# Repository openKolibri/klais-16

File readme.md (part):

![SIXTEEN]
![SEGMENT]
![DISPLAY]

# Sixteen Segment Display
The look of classic signage, be it neon tubes, wrought iron, or the use of distinctive typography and negative space, has a particular appeal. Unfortunately, the art form is dwindling due to the flexibility and flash that comes with newer LED arrays. Their distinctive styles have been giving way for the monotony of RGB LED panels.

![cycleGif]

The *Klais Display* series, in which this panel is the first item, was inspired by the early electronic displays still seen in relics bygone from an era of cigarette machines, electronics test equipment, and pinball machines. Its been modernized, enlarged, and made easily integrable into your own projects, while retaining its beauty and elegance.

![isoArray]

What follows below is highly detailed technical documentation. The [user guide][userGuide] is also available and focuses on integrating the display(s) into a project.

## Table of Contents
  * [Design](#design)
    * [Hardware](#hardware)
      * [LEDs](#leds)
      * [LED Driver](#led-driver)
      * [Microcontroller](#microcontroller)
      * [Power supply](#power-supply)
      * [Connections](#connections)
        * [Programming](#programming)
        * [Dataflow](#dataflow)
        * [Config Pads](#config-pads)
        * [Key Connector](#key-connector)
      * [Mounting](#mounting)
    * [Firmware](#firmware)
      * [Modes](#modes)
      * [UART](#uart)
        * [RX](#rx)
        * [TX](#tx)
      * [Brightness](#brightness)
      * [Timeout Refresh](#timeout-refresh)
      * [Display Driver](#display-driver)
        * [Protocol](#protocol)
        * [LED Number](#led-number)
        * [Segment Order](#segment-order)
      * [Configuration](#configuration)
        * [Baud Selection](#baud-selection)
      * [Compiling](#compiling)
      * [Flashing](#flashing)
  * [Absolute Maximum Ratings](#absolute-maximum-ratings)
  * [Guaranteed Ratings](#guaranteed-ratings)
  * [Manufacturing](#manufacturing)
    * [BOM](#bom)
    * [PCB-Assembly](#pcb-assembly)
    * [Physical Assembly](#physical-assembly)
    * [Production Scaling](#production-scaling)
      * [PCB Stack](#pcb-stack)
      * [Die Cut](#die-cut)
      * [Injection Moulding](#injection-moulding)
      * [Custom ASIC](#custom-asic)
    * [Programmer](#programmer)
      * [Minimal](#minimal)
      * [Production](#production)
    * [Artwork](#artwork)
    * [Labels](#labels)
    * [Inventory and QC](#inventory-and-qc)
    * [Part Numbers](#part-numbers)
  * [Safety](#safety)
  * [Certifications](#certifications)
  * [Licence](#licence)
  * [Attribution](#attribution)
    * [Fonts](#fonts)
    * [Libraries](#libraries)
  * [Reccomended Reading](#reccomended-reading)
  * [ToDo](#todo)

## Design
The display is a recreation of sixteen segment alphanumeric displays in a format that is physically larger and thinner than anything available on the viewing front. The modular segments can be combined to make a display of any length. It is designed to be easy to use and accessible. The physical design is based on stacking layers to provide clearance, a diffusion layer, and encapsulation for the electronics. The minimalist design and 3:2 aspect ratio were chosen to make integration very clean. There are no gaps between characters and when placed side-by-side, there is a flat near-seamless surface.

| NOON               | MDNT               | BASE               |
| ------------------ | ------------------ | ------------------ |
| ![SEG-16-RED-NOON] | ![SEG-16-RED-MDNT] | ![SEG-16-RED-BASE] |

### Hardware
The panels are designed for efficient high yield manufacturing in both small and large quantities, with three possible stages, based on tooling investment. The physical size of each panel is `100 mm` x `66.66 mm`, providing a 3:2 aspect ratio and are nominally `5.8 mm` thick. Each panel weighs `63.97 g` with 6 plastic rivets.

![schematic]

A [schematic.pdf] is also available.

#### LEDs
The assembly uses 128 0603 surface mount LEDs. They are spaced evenly through all the segments, as well as eight of them acting as points in the underline. The 0603 (`60 mil` x `30 mil`, or `1.5 mm` x `0.8 mm`) package is used for their wide accessibility, providing a breadth of alternatives in color, lens projection angle, and brightness for possible substitutions. The datasheets for the LEDs used for each model is provided in the table below.

| Model             | MPN        | Detail          | Current Draw         |
| ----------------- | ---------- | --------------- | -------------------- |
| `SEG-16-RED-XXXX` | [KT-0603R] | ![IMG-KT-0603R] | [RED][asciiCurrent]  |

#### Led Driver
Titan Micro Electronic's [TM1640] ([english][TM1640ENG]) is used to control the LEDs. The device provides individual control of 128 LEDs in a 16x8 multiplexing configuration, has 8 levels of brightness adjustment, and provides a constant current supply of `20 mA`. It is rated for only `5V` but testing shows that, although with a slightly lower multiplexing frequency, it works quite well at `3.3V`. Communication is over a clocked serial link with a custom protocol and register mappings control the outputs. The 16 grids are rows, while the eight segments are the columns.

![IMG-TM1640]

This chip is made specifically for the Chinese market and may be hard to source in the west. Based on datasheets, it is easily swappable with identical components from other manufacturers, as shown below, in case the availability changes.

| Manufacturer            | MPN      |
| ----------------------- | -------- |
| GN Semiconductors       | GN1640   |
| Cmsemicon               | CMS1640  |
| Wuxi I-CORE Electronics | AiP1640  |

#### Microcontroller
STMicroelectronics's [STM8S003] is a very low-cost microcontroller for cost sensitive applications, but provides a reasonable host of features. It has a wide voltage range of `2.95V` to `5.5V`, internal 16Mhz clock, UART that can be clocked at up to 1Mbps, plenty of timers, and 28 I/O. As well as other features that are not being used like a 10b ADC, SPI/I2C hardware, and low power modes.

![IMG-STM8S003]

#### Power supply
The input power is rated at `5V`, and the current drawn is dependent on the number of lit LEDs and the color of the display. Each segment has `100 uF` + `10 uF` of bulk capacitance, as well as decoupling on all the chips so it should be robust against a unstable power supply. There is no reverse polarity or overvoltage protection as that is the responsibility of the integrator. The table below shows some current draws, with the full table of all the models and characters [available][asciiCurrent] along with measurement methodology.

| Display  | `RED` Full Brightness (mA) | `RED` Min Brightness (mA) |
| -------- | --------------------------:| -------------------------:|
| Off      |                        5.2 |                       5.2 |
| All      |                      319.0 |                      28.6 |
| `@`      |                      197.0 |                      19.1 |
| `.`      |                       17.1 |                       6.0 |
| `K`      |                      125.7 |                      13.8 |
| `[`      |                      106.0 |                      12.4 |

Maximum power draw is `1.6 W` at max brightness and all segments lit. Temperature rise above ambient after two hours is `15.9°C` (`61°F`).

#### Connections
The back of the module contains pads that are used for communication and configuration, providing many options to the end-user.

![config-back]

##### Programming
The four labeled pads near the top of the module are for programming. The STM8S uses a `SWIM` programming interface. The `4 mm` round pads are used to install the initial firmware and can be used for firmware updates or custom firmware if needed. The power pins are connected to the power rails, so they can also be used as power input or outputs.

![config-pgrm]

##### Dataflow
The five pads on each side are the connections that provide the data, as well as power rails, from one board to another. For basic functionality, lining up the boards and soldering the top three pads (`GND`, `TX/RX`, and `+5V`) is all that is needed, although soldering all five will provide more power rails and cause no issues.

![config-dataflow]

With the display facing you, the data comes in on the left on the `RX` pad, and flows out on the right via the `TX` pad. If the modules are soldered inverted, the connection is symmetric providing protection against swapping power supply rails.

If needed, the inverted configuration also provides the option of having two decimal points forming a colon. For this configuration to work, the solder jumper pads on the back will need to be reconfigured, cutting the top two and bridging the bottom, as shown in the diagram.

![config-dataflowInv]

The moves the `RX` and `TX` lines to the correct sides to be placed inline with normally oriented modules.

##### Config Pads
The back has seven configuration pads that provide different settings and are checked on boot. By default, they are all unbridged. The configuration pads are to be selected with solder jumpers.

![config-config]

##### Key Connector
The front contains two optional unpopulated spring connectors Molex [0472861001]. These provide functionality if the thickness of the panel or reconfigurability is the main concern. By removing any solder joints on the back, and transmitting the data and power through the keyed connector. The thickness is limited to `5.8 mm`. The small PCB keys also allow assembly and construction of quick and easily reconfigurable arrays. The connectors are not always used, so they are not installed by default since they add cost and are not expected to be used by most.

![config-keyed]

The solder jumper marked `RTN_EN` enables the return channel on the last board. If a chain of displays is used and needs to be chained to the next row, this will send the signal back though one of the spring connector pins and make it available on the first display making a for a cleaner run of signal between rows.

#### Mounting
The mounting holes are placed `3 mm` from all edges and are for `M3` screws in a very close fit with a `3.1 mm` drill and though plated for a bit more ruggedness. A `#4` screw can be used as a imperial alternative. They are not connected to any nets, have a `5.5 mm` annular ring for screw heads, and are masked so if screws are not used, the annular ring surface matches the rest of the panel.

![mountingDim]

The holes and hardware provide a number of options for assembly and mounting.

| Mounting Method              | Part Number                                      | Component         | Example               |
| ---------------------------- | ------------------------------------------------ | ----------------- | --------------------- |
| Push Rivet `3 mm` x `7.5 mm` | [R3075]                                          | ![plasticRivet]   | ![rivetInstalled]     |
| Spring pin `3 mm` x `6 mm`   | [97161A128]                                      | ![springPin]      | ![springPinInstalled] |
| `M3x8x0.5` and Nut           | [91292A112] [91828A211]                          | ![M3x8]           | ![M3x8Installed]      |
| `15 mm` Extrusion M3x10      | [Misumi HFS3], [OpenBeam], [Makerbeam XL]        | ![openbeamParts]  | ![openbeamInstalled]  |
| `10 mm` Extruison M3x8       | [MakerBeam], [MicroRAX]                          | ![makerbeamParts] | ![makerbeamInstalled] |
| `20 mm` Extrusion Slot       | [Misumi HFS5], [Metric 8020]                     | ![2020Extrusion]  | ![2020Installed]      |
| Soldered brass nut           | [90690A037]                                      |                   |                       |
| Zip Ties `3 mm`              |                                                  |                   |                       |
| #4 screw, machine or wood    |                                                  |                   |                       |
| Pop rivets, M3 or #4         |                                                  |                   |                       |

### Firmware
The firmware is written in C and is fully interrupt driven. It uses the [STM8 standard periphiral library][STM8SPL] (SPL) and provides multiple modes of controlling the display through commands. All code shown is simplified pseudocode.

#### Modes
By default the display boots in the `ASCII` character mode operating as a state-machine making changes based on each byte received. When enough bytes have been received for the command, the device shifts back into `ASCII` mode.

| Mode       | Control Byte | Bytes | Notes                       |
| ---------- | ------------ | -----:| --------------------------- |
| ASCII      | None         |     0 | Displays ASCII cahrachter   |
| Segment    | 0x11 `DC1`   |     3 | Control individual segments |
| LED        | 0x12 `DC2`   |    16 | Control individual LEDs     |
| Brightness | 0x13 `DC3`   |     1 | Set brightness              |

**Only ASCII mode is verified in firmware version 0.6 other modes are in beta**

#### UART
The UART hardware is used to receive and transmit data from a module to another. Communication is through an 8 bit NRZ with one start bit and one stop bit encoding with no parity and the default baud rate is `115200 bps`. The voltage levels are the module power voltage, nominally `5V`.

The UART is initialized on boot and the receive interrupt is enabled. When a new character has been read in the receive buffer, the interrupt fires.

##### RX
Based on the receive mode the new data is loaded into the receive buffer. A number of consecutive bytes read is dependent on the mode that is set. A mode byte received after mode has been reset will change the mode as well. The transmit interrupt is fired when a new byte is received and the buffer is full, depending on the current receive mode.

##### TX
The first byte is sent by the interrupt trigger. Depending on the transmit mode, the interrupts continue to fire, stepping down through the buffer until it is empty, outputting the data in the same order as it was received.

#### Brightness
There are nine brightness levels including blanking. They are accessed with sending the brightness mode selector followed by the brightness code.

| Level | Code (HEX) | Code (DEC) |
| -----:| ---------- | ----------:|
|   OFF | 0x81       |        129 |
|     1 | 0x88       |        136 |
|     2 | 0x89       |        137 |
|     4 | 0x8A       |        138 |
|    10 | 0x8B       |        139 |
|    11 | 0x8C       |        140 |
|    12 | 0x8D       |        141 |
|    13 | 0x8E       |        142 |
|    14 | 0x8F       |        143 |

#### Timeout Refresh
A display refresh timeout is implemented so the display only updates when there is a pause in the data. This prevents the display from flickering with intermediate data when a stream of data is being loaded into an array. This also updates all displays at the exact same time, since the time from the last byte is the same across all displays in an array.

```c
UART_RX_INTERRUPT() {
  TIMER_SET(0x00);
  TIMER(INTERRUPT, ENABLE);

  // Remaining RX routine ...
}
```

Every time a new character is received in the RX buffer, a timeout is started of 1 ms (*to be replaced with 2.5 byte time based on baud rate*). If a new character comes before the timeout is reached, it is reset again. When the timeout is reached, the overflow interrupt is triggered. In the interrupt, the further interrupts are disabled and then the display is drawn based on the TX mode.

```c
TIMER_INTERRUPT(){
  TIMER(INTERUPT, DISABLE);
    switch (txMode) {
        case LED_CONTROL:
          showLeds(data);
          break;
        case SEGEMENT_CONTROL:
          showSegments(data);
          break;
        case BRIGHTNESS_CONTROL:
          setBrightness(data);
          break;
        default:
          showLetter(data);
    }
}
```

#### Display Driver
The display driver is a minimal custom library. The display driver is controlled over a clocked serial link with a custom protocol. The LEDs are multiplexed based on the internal memory that stores a 1b value for each LED.

The chip has only a few registers, most of which make up the current LED states. They are all described in the header file and fall into three sections.

- Data Commands
- Grid Memory
- Display Brightness

##### Protocol
A few requirements define the protocol.

- Default state for both clock and data is high
- Start condition is data going low followed by clock going low
- A bit is read when the clock is pulsed positive
- Data cannot change while clock is high
- End condition is clock high followed by data high
- 8 bits per byte, LSB First

![TM1640Timing]

Registers are set by sending a command byte followed by a optional data byte based on the command. A set of commands can be sent if auto increment mode is set by not fulfilling the end condition and sending the next byte immediately.

![dataCapImg]

A Saleae logic [capture][dateCapFile] is also provided.

##### LED Number
The LEDs are placed in a grid-like pattern, so a conversion is needed to map each LED to the segment it's in. [segmentMapping.h] contains arrays that map the LED's reference designator to each segment. This still needs to be converted into the segments and grid from the LED number. The formula below is used to make those conversions.

```
GRID = ((REF-1) / 8) + 1
SEG = (REF-1) % 8
```

##### Segment Order
Besides direct control over the LEDs, there are also helper functions such as segment control and print letter. These use the [segmentMapping.h] and [sixteenSegments.h] headers. Once the LEDs are mapped to the segments, the segments are mapped to the ASCII character set. [sixteenSegments.h] contains which segments need to be lit for each character, the notation used in both files refers to the segments in clockwise order going in as-is conversion with sixteen segment displays.

![segmentMap]

#### Configuration
On boot, the seven GPIO for the configuration pads have their internal pullups enabled and are then set as inputs. They are all sampled. Any that have been bridged to ground will read as low and their inverted state can be used to set the configuration.

```c
  uint8_t config = 0x00;
  config |= !read(PIN_0) << 0;
  config |= !read(PIN_1) << 1;
  config |= !read(PIN_2) << 2;
  config |= !read(PIN_3) << 3;
  config |= !read(PIN_4) << 4;
  config |= !read(PIN_5) << 5;
  config |= !read(PIN_6) << 6;
```

The pads have functions attached to them, some are just switches, while others join together in a binary segment to allow multiple selections.

| Pad | Function         | Status               |
| ---:| ---------------- | -------------------- |
|   0 | Inverted Display | Not implemented      |
|   1 | Baud (Bit 3)     | Implemented in 0.6   |
|   2 | Baud (Bit 2)     | Implemented in 0.6   |
|   3 | Baud (Bit 1)     | Implemented in 0.6   |
|   4 | Baud (Bit 0)     | Implemented in 0.6   |
|   5 | Pending          | Open for Development |
|   6 | Pending          | Open for Development |

##### Baud Selection
Pads `[4:1]` allow baud selection, the default is `115200` as it is a common bitrate that is available on most computer and microcontrollers and is reasonably fast for most applications.

| Pad 4 | Pad 3 | Pad 2 | Pad 1 | Selected Baud |
| -----:| -----:| -----:| -----:| -------------:|
|     0 |     0 |     0 |     0 |        115200 |
|     0 |     0 |     0 |     1 |           110 |
|     0 |     0 |     1 |     0 |           300 |
|     0 |     0 |     1 |     1 |           600 |
|     0 |     1 |     0 |     0 |          1200 |
|     0 |     1 |     0 |     1 |          2400 |
|     0 |     1 |     1 |     0 |          4800 |
|     0 |     1 |     1 |     1 |          9600 |
|     1 |     0 |     0 |     0 |         19200 |
|     1 |     0 |     0 |     1 |         38400 |
|     1 |     0 |     1 |     0 |         57600 |
|     1 |     0 |     1 |     1 |        128000 |
|     1 |     1 |     0 |     0 |        230400 |
|     1 |     1 |     0 |     1 |        256000 |
|     1 |     1 |     1 |     0 |        460800 |
|     1 |     1 |     1 |     1 |       1000000 |

It is tested with a 4 bit mask and right-shifted to get numbers 0-15 from the config byte.
```c
uint32_t bauds[16] = {115200, 110, /*...*/, 460800, 1000000};
uint32_t baud = bauds[(config & 0X1E) >> 1];
```

#### Compiling
It is setup to be compiled through [PlatformIO]. More information can be found through its [documentation][platformIODocs]. Changes may be made to the settings in the `ini` file.

#### Flashing
The [programming pads](#programming) on the back are used to program the module. An ST-Link V2 with the SWIM protocol is used to upload the firmware.

Uploading using PlatformIO is currently used. Refer to [documentaiton][platformIODocs]. Changes may be needed to the `ini` file settings.

We also use a custom bash script internally that uploads, tests, and updates our database. It uses STM8Flash on Linux machines and ST Visual Programmer on WSL.

## Absolute maximum ratings
**To be tested, don't have the power supply, or really the heart to kill a module just yet.**

Works fine down to 3.3V.

## Guaranteed ratings

| Mesurement   | Value | Unit | Tolerence |
| ------------ | -----:| ---- | --------- |
| Power Supply |   5.0 | V    | ± 0.2     |
| Max current  |   319 | mA   | ± 5%      |
| Max Temp     |    60 | C    |           |
| Min Temp     |   -20 | C    |           |

## Manufacturing
Designing for manufacturing was a large portion of this project. This was done through many approaches on a number of fronts.

### BOM
The BOM was selected with parts that are common to the Chinese high-volume manufacturing market, have strong supply chains, as well as many alternatives in case a supplier stops manufacture. The number of unique parts was kept to a minimum and the maximum amount of features can be implemented with "free" options, like SMD pads. The table of BOM is shown below.

| REF       | QTY | Manufacturer               | MPN              | Description                                 |
| --------- | ---:| -------------------------- | ---------------- | ------------------------------------------- |
| C1        |   1 | AVX                        | TAJB107K006RNJ   | CAP: Tantalum 100uF 6.3V CASE-B_3528        |
| C2        |   1 | AVX                        | TAJA106K016RNJ   | CAP: Tantalum 10uF 16V CASE-A_3216          |
| C3 C6     |   3 | Samsung Electro-Mechanics  | CL05A105KA5NQNC  | CAP: MLCC 1uF 25V 0402                      |
| C4 C5 C7  |   2 | Samsung Electro-Mechanics  | CL05B104KO5NNNC  | CAP: MLCC 100nF 16V 0402                    |
| D1-D128   | 128 | Hubei KENTO Elec           | KT-0603R         | LED: RED 520-625nm 90-100mcd@20mA 0603      |
| R1 R2     |   2 | Uniroyal Elec              | 0402WGF1002TCE   | RES: 10K 1% 1/16W 0402                      |
| U1        |   1 | STMicroelectronics         | STM8S003F3P6TR   | MCU: 8b 16Mhz 8k Flash 128B EEPROM TSSOP-20 |
| U2        |   1 | Shenzhen Titan Micro Elec  | TM1640           | DRV: 16x8 LED Driver SOP-28                 |

The [Octopart] BOM is also available, although not much use since the parts are not carried by US distributors.

### PCB-Assembly
The PCB assembly is single-sided surface mount components only. The smallest components are 0402. All can be PNP from tapes or tubes, and reflowed at once. There are three fiducials as well as three tooling holes on each board. The tooling holes are `1.152 mm` and the fiducials are `1.5 mm` x `3 mm`. There are 139 components all of which are SMD, yielding a total of 322 solder joints.

![assembly]

### Physical Assembly
The panels are combined in order and can be held together with `3 mm` x` 7.5 mm` nylon 6/6 push rivets. This makes ingress into inventory much faster, and gives the customer another option to use for mounting since it's an uncommon part.

### Production Scaling
The physical assembly varies in the volume of production. Further sections will be updated with information if we ever reach those volumes.

#### PCB Stack
First iteration is the PCB stack as that has no tooling cost and all can be order from the same manufacturer. There are four PCBs in the stack that make-up the display.

| Board | Height (mm) | Width (mm) | Layers | Copper  | Thickness (mm) | Material | Min Drill (mm) | Trace Sizing | Mask  | Silk   | E-Test |
| ----- | -----------:| ----------:| ------:| -------:| --------------:| -------- | --------------:| ------------:| ----- | ------ | ------ |
| L0    |      100.00 |      66.66 |      2 |  1.0 oz |            1.0 | FR4      |            0.3 |          6/6 | Green |  White | Yes    |
| L1    |      100.00 |      66.66 |      2 |  1.0 oz |            1.6 | FR4      |            N/A |          N/A | Black |  White | No     |
| L2    |      100.00 |      66.66 |      2 |  1.0 oz |            1.6 | FR4      |            N/A |          N/A | Black |  White | No     |
| L3    |      100.00 |      66.66 |      2 |  1.0 oz |            1.6 | FR4      |            N/A |          N/A | Black |  White | No     |

The bottom board is the electrical board containing all the components and signals, and is used for all iterations. The following two boards provide spacing and separation for the diffusion of the LEDs, as well as cut outs for the other components, and the final board provides diffusion and a solid panel for the front face. The layout of each layer is shown in the table below.

|   L0  |   L1  |   L2  |   L3  |
|:-----:|:-----:|:-----:|:-----:|
| ![L0] | ![L1] | ![L2] | ![L3] |

PCB stack is best for quantities below 500 units.

#### Die Cut
The die cut panels replace the top three panels with `1/16"` plastic that is die cut. This is faster to manufacture and less expensive, since we do not need the copper, silk, or mask layers. Also, uses a through-opaque material instead of the FR4 providing better protection from light bleed.

|     L1    |     L2    |     L3    |
|:---------:|:---------:|:---------:|
| ![L1-DIE] | ![L2-DIE] | ![L3-DIE] |

Switch to die cut at 1k-10k units.

#### Injection Moulding
Injection moulded panel will replace the front three panels with a single injection moulded plastic part, as well as the screws. Providing the option to either punch through from the front to get the same M3 holes, or screw in from the back to have a completely clean front panel. The IM part also provides other benefits, such as, a more consistent texture on the whole panel, and a high contrast front that has no discernible pattern when off.

![imProto]

A test model was made with 2.5 deg draft angles and `1.2 mm` wall thickness for ABS moulding. Approximate calculations show tooling costs of $7.5k for production steel tooling, and 15s cycle time.

Switch to IM at 20k-100k units.

#### Custom ASIC
Flipchip LEDs with COB fully integrated controller. HDL gateware design to begin at 50k units. RISC-V processor with 16x16 multiplexing LED array at a 72 MHz PLL clock.

[Hey, a girl can dream. Chip die image]

Engineering and silicon die cost around $50k tooling (maybe? I don't really know, but I could probably synthesize a sea of gates design that works) Switch to custom ASIC at 100k units.

### Programmer
The chip needs to be programmed with the firmware and tested for proper operation before sending out to customers. Two programmers are designed. First, a low cost simple programmer for smaller quantities and available on special request for those who want to customize the firmware, and the other is a completely independent production-ready programmer and tester.

#### Minimal
Them minimal program has holes for alignment corresponding to the top row, and four spring pins. These connect out to the programming header which can then be corrected to an ST-Link V2. The alignment holes have M3x8 screws and nuts which were added to create alignment pins. The board to be programmed is aligned with the pin and held down while programming.

![minimalProgrammer]

#### Production
The production programmer is a program and test jig. The boards are slipped under the bottom overhang and pushed down until the lever snaps and holds them in place. Then a full test suite can be run, checking the input and output, programming with multiple firmwares and reading back system outputs to verify that the device works properly.

![productionProgrammer]

### Artwork
The artwork on the back is a trademark and protected by copyright. This can not be duplicated on derivative works. It consists of the Kolibri bird, copyright and designer notices, certifications, a location for labeling, as well as the URL and QR code to documentation.

### Labels
The back has a location for a `38 mm` x `13 mm` label from a Brother `38 mm` continuous label. This label can have serial number, batch numbers, the model number, and any other device specific information.

![config-label]

### Inventory and QC
Inventory can then be managed with QR coded serialized tags. The serialization also provides better QC as it allows failure analysis and tracking in case of issues traceable to the batch and assembly level.

### Part Numbers
The manufacturer part number is based on the following scheme.

MPN: `SEG-16-AAA-BBBB`

Where `AAA` is the three character code for color

| Code   | Color              |
| ------ | ------------------ |
| `RED`  | Red                |
| `GRN`  | Green              |
| `BLU`  | Blue               |
| `RGB`  | Red Green Blue     |
| `WHT`  | White (5000k)      |
| `WWT`  | Warm White (3500k) |
| `YEL`  | Yellow             |

And `BBBB` denotes the face type

| Code   | Face Type                       |
| ------ | ------------------------------- |
| `NOON` | Noon face, Exposed FR4          |
| `MDNT` | Midnight face. Black soldermask |
| `PLEX` | Acrylic Laser Cut               |
| `IM  ` | Injection Moulded               |

## Safety
The assembly is almost exclusively made from FR4. It is highly fire retardant and will not burn after a flame is removed.

The edges are milled, but it is possible to have small pieces that could cause cuts, abrasions, or become embedded in the skin. If sanding or milling the board, use a respirator as fiberglass dust is carcinogenic.

The boards are assembled in a lead-free process and all components are RHOS certified.

The low voltage `3.0`-`5.5V` as well as the currents used pose very little risk to healthy humans.

## Certifications
Certifications take time and effort but will make a better product by guaranteeing its safety to users and let them use it in other projects. The table below shows the order we will be trying to obtain certifications.

| Cetrtifing Authority     | Status                    |
| -------------------------| ------------------------- |
| OSHW                     | [DE000087]                |
| CE                       | No  (Self Certification)  |
| FCC                      | No  (Self Certification)  |
| UL Registered Component  | No  (yearly fee)          |
| WEEE                     | No  (yearly fee)          |

## Licence
The product was designed by Sawaiz Syed for Kolibri who owns the copyright. Everything is released under permissive copyleft licenses, and copies of all licenses are included.

| Sector        | License      | Verison |
| ------------- | ------------ | -------:|
| Hardware      | [CERN-OHL-S] |     2.0 |
| Firmware      | [GNU GPL]    |     3.0 |
| Documentation | [CC BY-SA]   |     4.0 |

Copies of all licenses are required with the distribution of files. All files are available in easy-to-modify types for remixing. Please purchase original products from Kolibri to support further products, design, and research.

## Attribution
As with everything, this too is built on the gracious support of previous projects.

- KiCad
- Inkscape
- Blender
- SDCC
- STM8Flash
- PlatfromIO

### Fonts
- [DejaVu]
- [IBM Plex Mono]

### Libraries
- [Sixteen Segment ASCII](https://github.com/dmadison/LED-Segment-ASCII) - MIT - Copyright (c) 2017 David Madison
- STM8 SPL (Available component, but not included)

## Recommended Reading

## Todo
- [ ] Switch from SPL to just C and registers or [open headers](https://github.com/gicking/STM8_headers)
- [ ] Change from PlatformIO to a makefile
- [ ] Implement inverted font

<!-- Files -->
[KT-0603R]:               ./pcb/SEG-16-XXX-XXXX-L0/components/KT-0603R/KT-0603R.pdf
[TM1640]:                 ./pcb/SEG-16-XXX-XXXX-L0/components/TM1640/TM1640.pdf
[TM1640ENG]:              ./pcb/SEG-16-XXX-XXXX-L0/components/TM1640/TM1640-ENG.pdf
[STM8S003]:               ./pcb/SEG-16-XXX-XXXX-L0/components/STM8S003/STM8S003.pdf
[0472861001]:             ./pcb/SEG-16-XXX-XXXX-L0/components/0472861001/0472861001.pdf
[schematic.pdf]:          ./pcb/SEG-16-XXX-XXXX-L0/SEG-16-XXX-XXXX-L0.pdf
[segmentMapping.h]:       ./firmware/include/segmentMapping.h
[sixteenSegments.h]:      ./firmware/include/sixteenSegments.h

<!-- Links -->
[Octopart]:               https://octopart.com/bom-tool/6sdiCse8
[97161A128]:              https://www.mcmaster.com/97161A128
[91292A112]:              https://www.mcmaster.com/91292A112
[91828A211]:              https://www.mcmaster.com/91828A211
[90690A037]:              https://www.mcmaster.com/90690A037
[R3075]:                  https://www.amazon.com/gp/product/B07Z1XCS3M/ref=ppx_yo_dt_b_asin_title_o00_s00?ie=UTF8&psc=1
[Misumi HFS3]:            https://us.misumi-ec.com/vona2/detail/110300465870/
[Misumi HFS5]:            https://us.misumi-ec.com/vona2/detail/110302683830
[MakerBeam]:              https://www.makerbeam.com/makerbeam/makerbeam-10x10mm-profile-lengths-anodised-in-clea/
[Makerbeam XL]:           https://www.makerbeam.com/makerbeamxl/makerbeamxl-15x15mm-profile-lengths-anodised-in-cl/
[OpenBeam]:               https://www.makerbeam.com/openbeam/openbeam-15x15mm-profile-lengths-anodised-in-black/
[MicroRAX]:               http://www.microrax.com/
[Metric 8020]:            https://8020.net/20-2020.html
[STM8SPL]:                https://www.st.com/en/embedded-software/stsw-stm8069.html
[PlatformIO]:             https://platformio.org/
[platformIODocs]:         https://docs.platformio.org/en/latest/

<!-- Internal Links -->
[userGuide]:              ./docs/userGuide.md
[asciiCurrent]:           ./docs/asciiCurrent.md
[configTable]:            ./docs/configTable.md

<!-- Images -->
[SIXTEEN]:                ./docs/title/SIXTEEN.png                                               "SIXTEEN Rendered on display"
[SEGMENT]:                ./docs/title/SEGMENT.png                                               "SEGMENT Rendered on display"
[DISPLAY]:                ./docs/title/DISPLAY.png                                               "DISPLAY Rendered on display"
[isoArray]:               ./docs/product/isoArray.jpg                                            "Isometric view of a few panels lit with time"
[SEG-16-RED-NOON]:        ./docs/product/SEG-16-RED-NOON.jpg                                     "Top view of a NOON"
[SEG-16-RED-MDNT]:        ./docs/product/SEG-16-RED-MDNT.jpg                                     "Top view of a MDNT"
[SEG-16-RED-BASE]:        ./docs/product/SEG-16-RED-BASE.jpg                                     "Top view of a BASE"
[angledShow]:             ./docs/product/angledShow.jpg                                          "Angled shot of two panels"
[cycleGif]:               ./docs/char/char8M.gif                                                 "Animated gif of full ASCII cycle"
[schematic]:              ./docs/assembly/schematic.png                                          "Full schematic of design"

<!-- Config -->
[config-back]:            ./docs/config/backPanel.jpg                                            "View of entire back panel"
[config-pgrm]:            ./docs/config/pgrm.jpg                                                 "Detail of the program pads"
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
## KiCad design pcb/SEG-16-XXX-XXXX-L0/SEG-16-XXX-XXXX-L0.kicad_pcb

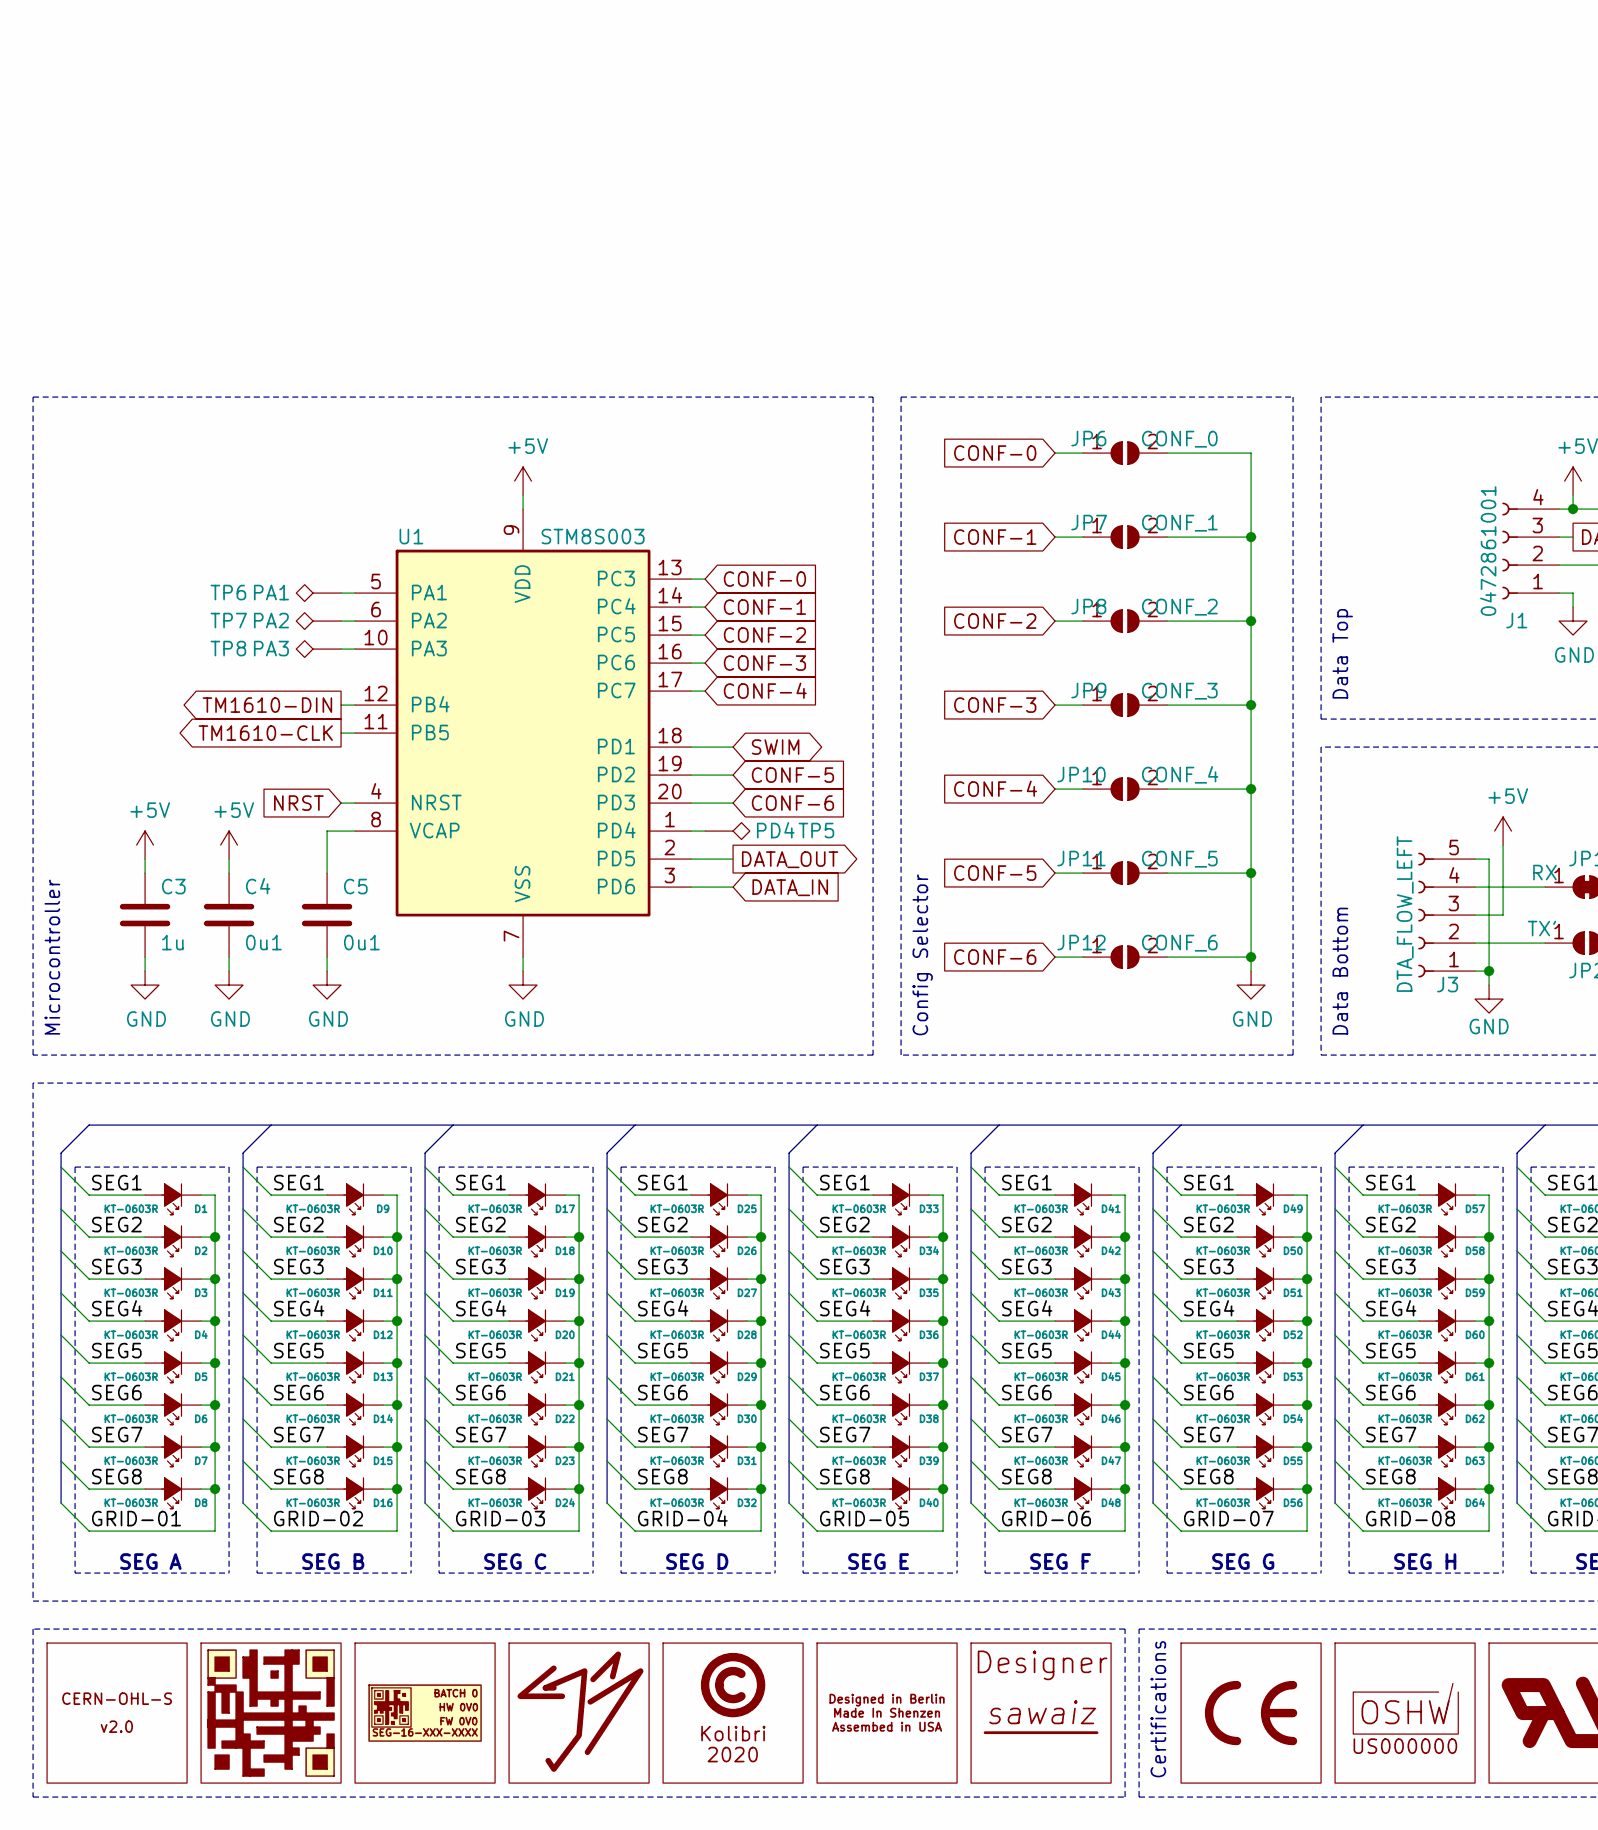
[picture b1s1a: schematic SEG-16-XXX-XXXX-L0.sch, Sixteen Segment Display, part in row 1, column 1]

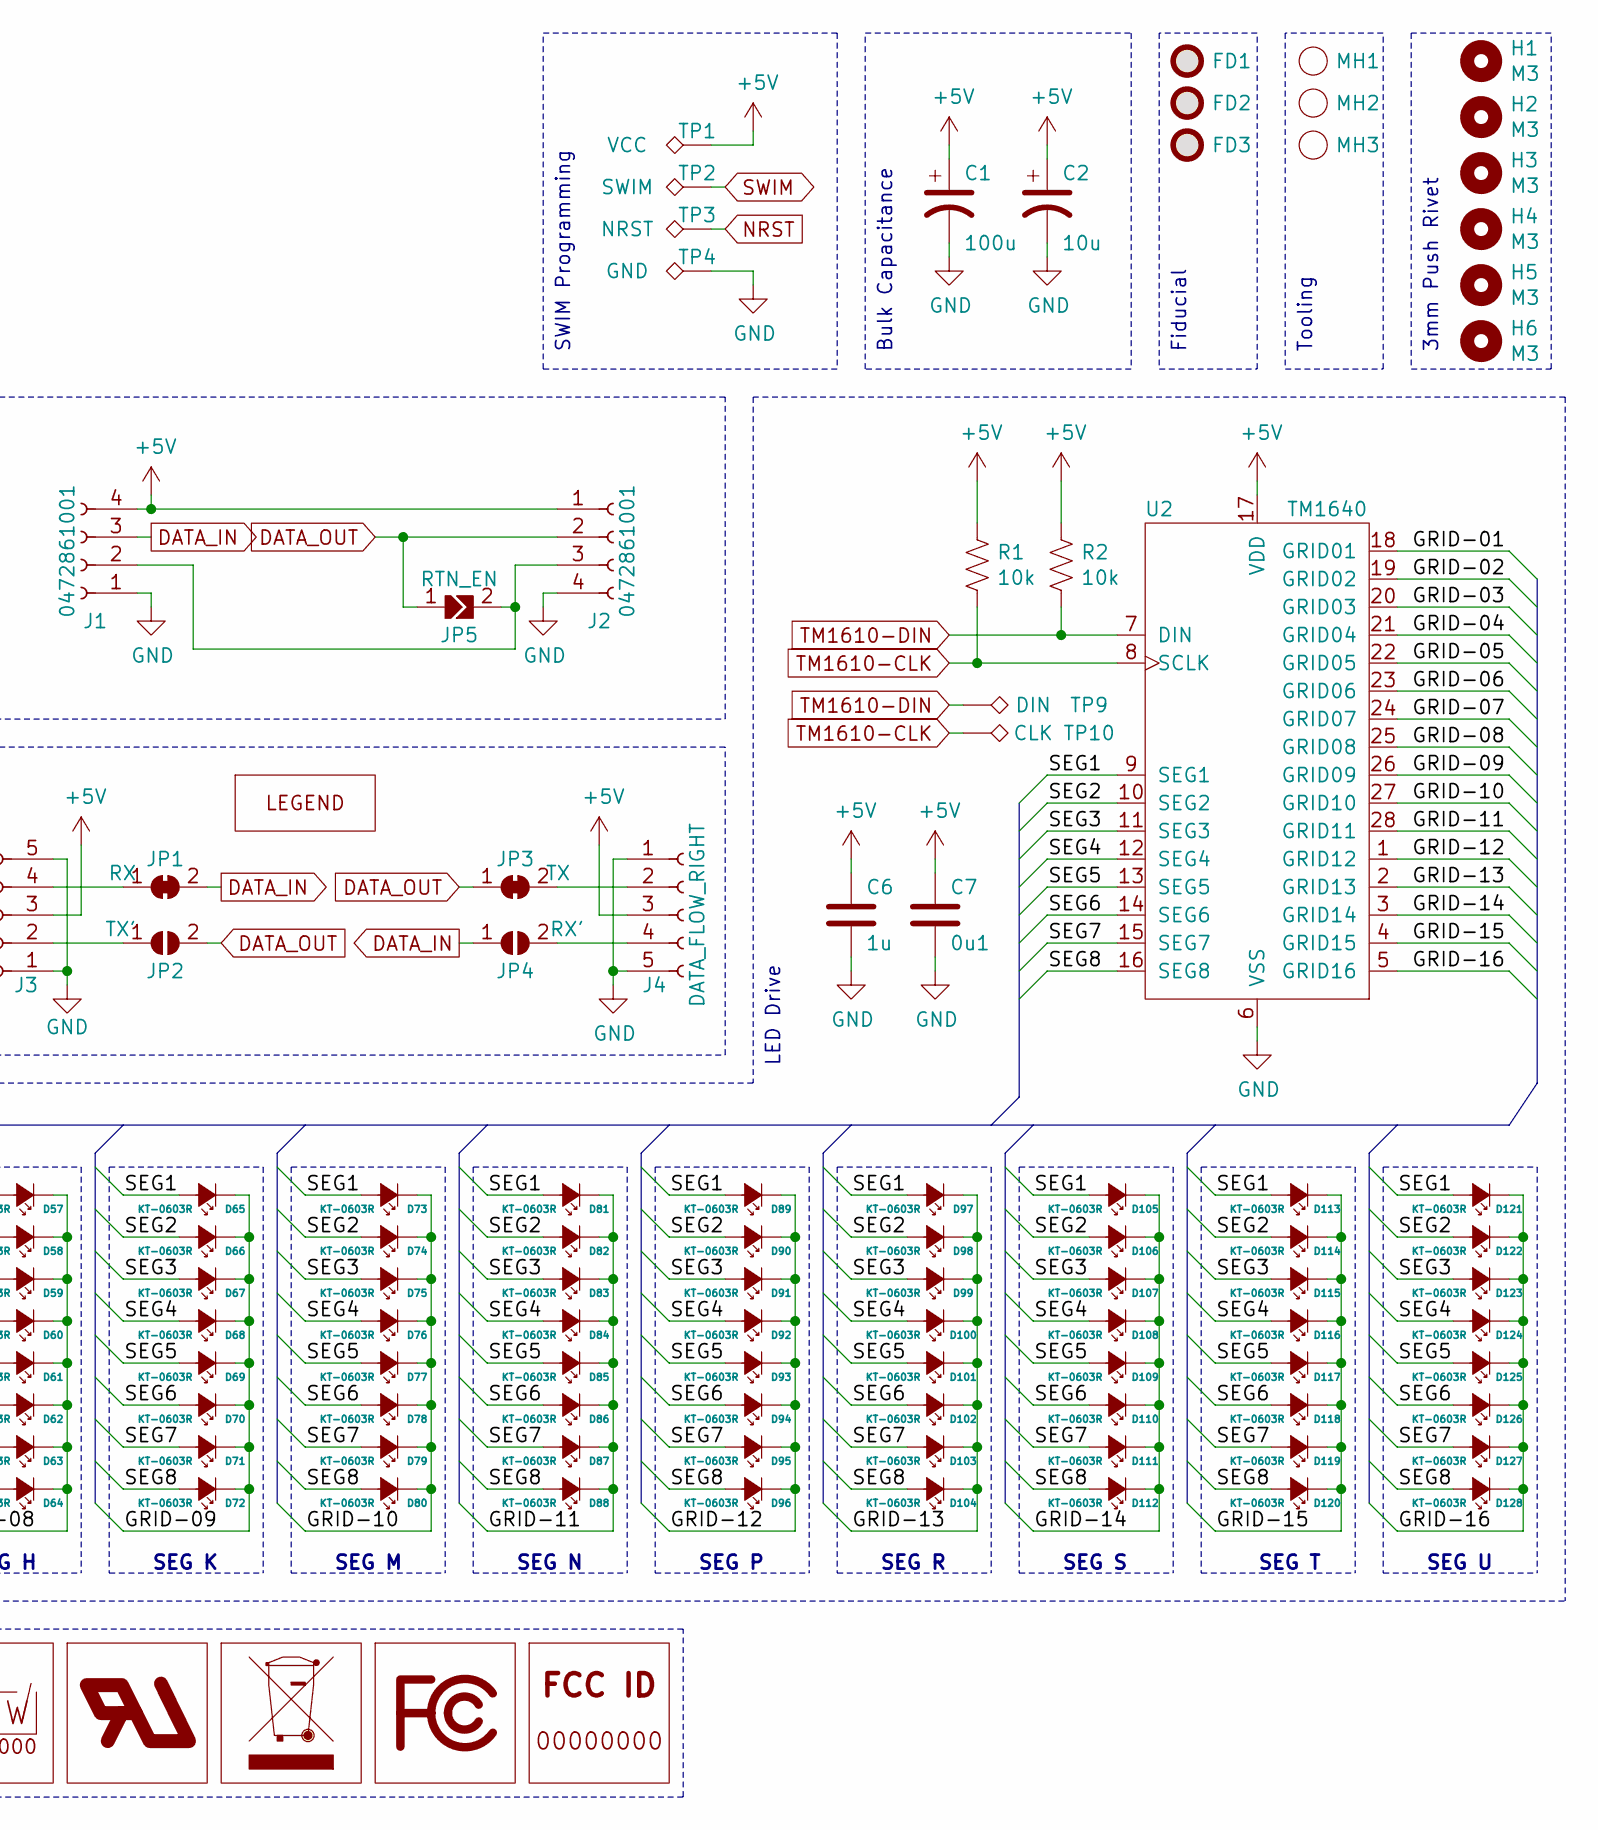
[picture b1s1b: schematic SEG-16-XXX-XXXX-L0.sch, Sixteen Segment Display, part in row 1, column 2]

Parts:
C1: 100u; TAJB
C2: 10u; TAJA
C3, C6: 1u; C_0402
C4, C5, C7: 0u1; C_0402
D1, D2, D3, D4, D5, D6, D7, D8, D9, D10, D11, D12, D13, D14, D15, D16, D17, D18, D19, D20, D21, D22, D23, D24, D25, D26, D27, D28, D29, D30, D31, D32, D33, D34, D35, D36, D37, D38, D39, D40, D41, D42, D43, D44, D45, D46, D47, D48, D49, D50, D51, D52, D53, D54, D55, D56, D57, D58, D59, D60, D61, D62, D63, D64, D65, D66, D67, D68, D69, D70, D71, D72, D73, D74, D75, D76, D77, D78, D79, D80, D81, D82, D83, D84, D85, D86, D87, D88, D89, D90, D91, D92, D93, D94, D95, D96, D97, D98, D99, D100, D101, D102, D103, D104, D105, D106, D107, D108, D109, D110, D111, D112, D113, D114, D115, D116, D117, D118, D119, D120, D121, D122, D123, D124, D125, D126, D127, D128: KT-0603R
FD1, FD2, FD3: Fiducial; Fiducial_1.5mm_Mask3mm
H1, H2, H3, H4, H5, H6: M3; M3-3.1-Tented
J1, J2: 0472861001
J3: DTA_FLOW_LEFT; dataFlowConnector
J4: DATA_FLOW_RIGHT; dataFlowConnector
JP1: RX; SolderJumper-2_P1.3mm_Bridged_RoundedPad1.0x1.5mm
JP2: TX'; SolderJumper-2_P1.3mm_Open_RoundedPad1.0x1.5mm
JP3: TX; SolderJumper-2_P1.3mm_Bridged_RoundedPad1.0x1.5mm
JP4: RX'; SolderJumper-2_P1.3mm_Open_RoundedPad1.0x1.5mm
JP5: RTN_EN; SolderJumper-2_P1.3mm_Open_TrianglePad1.0x1.5mm
JP6: CONF_0; SolderJumper-2_P1.3mm_Open_RoundedPad1.0x1.5mm
JP7: CONF_1; SolderJumper-2_P1.3mm_Open_RoundedPad1.0x1.5mm
JP8: CONF_2; SolderJumper-2_P1.3mm_Open_RoundedPad1.0x1.5mm
JP9: CONF_3; SolderJumper-2_P1.3mm_Open_RoundedPad1.0x1.5mm
JP10: CONF_4; SolderJumper-2_P1.3mm_Open_RoundedPad1.0x1.5mm
JP11: CONF_5; SolderJumper-2_P1.3mm_Open_RoundedPad1.0x1.5mm
JP12: CONF_6; SolderJumper-2_P1.3mm_Open_RoundedPad1.0x1.5mm
MH1, MH2, MH3: toolingHole; 1.152mm-ToolingHole
MK1: CERN-OHL-S_V2.0; CERN-OHL-S_v2.0
MK2: SEG-16-QR
MK3: label
MK4: kolibriBird
MK5: copyright
MK6: designedMadeAssembled
MK7: designer
MK8: CE
MK9: OSHW
MK10: UL
MK11: WEEE
MK12: FCC
MK13: FCCID
MK14: legend
R1, R2: 10k; R_0402
TP1: VCC; TestPoint_Pad_D4.0mm
TP2: SWIM; TestPoint_Pad_D4.0mm
TP3: NRST; TestPoint_Pad_D4.0mm
TP4: GND; TestPoint_Pad_D4.0mm
TP5: PD4; TestPoint_Pad_D1.0mm
TP6: PA1; TestPoint_Pad_D1.0mm
TP7: PA2; TestPoint_Pad_D1.0mm
TP8: PA3; TestPoint_Pad_D1.0mm
TP9: DIN; TestPoint_Pad_D1.0mm
TP10: CLK; TestPoint_Pad_D1.0mm
U1: STM8S003; STM8S003-TSSOP20-6.5x6.4mm
U2: TM1640; SOP28-17.7x7.65

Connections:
+5V: C1.1, C2.1, C3.1, C4.1, C6.1, C7.1, J1.4, J2.1, J3.3, J4.3, R1.1, R2.1, TP1.1, U1.9 (VDD), U2.17 (VDD)
/GRID-01: D1.1 (K), D2.1 (K), D3.1 (K), D4.1 (K), D5.1 (K), D6.1 (K), D7.1 (K), D8.1 (K), U2.18 (GRID01)
/GRID-02: D9.1 (K), D10.1 (K), D11.1 (K), D12.1 (K), D13.1 (K), D14.1 (K), D15.1 (K), D16.1 (K), U2.19 (GRID02)
/GRID-03: D17.1 (K), D18.1 (K), D19.1 (K), D20.1 (K), D21.1 (K), D22.1 (K), D23.1 (K), D24.1 (K), U2.20 (GRID03)
/GRID-04: D25.1 (K), D26.1 (K), D27.1 (K), D28.1 (K), D29.1 (K), D30.1 (K), D31.1 (K), D32.1 (K), U2.21 (GRID04)
/GRID-05: D33.1 (K), D34.1 (K), D35.1 (K), D36.1 (K), D37.1 (K), D38.1 (K), D39.1 (K), D40.1 (K), U2.22 (GRID05)
/GRID-06: D41.1 (K), D42.1 (K), D43.1 (K), D44.1 (K), D45.1 (K), D46.1 (K), D47.1 (K), D48.1 (K), U2.23 (GRID06)
/GRID-07: D49.1 (K), D50.1 (K), D51.1 (K), D52.1 (K), D53.1 (K), D54.1 (K), D55.1 (K), D56.1 (K), U2.24 (GRID07)
/GRID-08: D57.1 (K), D58.1 (K), D59.1 (K), D60.1 (K), D61.1 (K), D62.1 (K), D63.1 (K), D64.1 (K), U2.25 (GRID08)
/GRID-09: D65.1 (K), D66.1 (K), D67.1 (K), D68.1 (K), D69.1 (K), D70.1 (K), D71.1 (K), D72.1 (K), U2.26 (GRID09)
/GRID-10: D73.1 (K), D74.1 (K), D75.1 (K), D76.1 (K), D77.1 (K), D78.1 (K), D79.1 (K), D80.1 (K), U2.27 (GRID10)
/GRID-11: D81.1 (K), D82.1 (K), D83.1 (K), D84.1 (K), D85.1 (K), D86.1 (K), D87.1 (K), D88.1 (K), U2.28 (GRID11)
/GRID-12: D89.1 (K), D90.1 (K), D91.1 (K), D92.1 (K), D93.1 (K), D94.1 (K), D95.1 (K), D96.1 (K), U2.1 (GRID12)
/GRID-13: D97.1 (K), D98.1 (K), D99.1 (K), D100.1 (K), D101.1 (K), D102.1 (K), D103.1 (K), D104.1 (K), U2.2 (GRID13)
/GRID-14: D105.1 (K), D106.1 (K), D107.1 (K), D108.1 (K), D109.1 (K), D110.1 (K), D111.1 (K), D112.1 (K), U2.3 (GRID14)
/GRID-15: D113.1 (K), D114.1 (K), D115.1 (K), D116.1 (K), D117.1 (K), D118.1 (K), D119.1 (K), D120.1 (K), U2.4 (GRID15)
/GRID-16: D121.1 (K), D122.1 (K), D123.1 (K), D124.1 (K), D125.1 (K), D126.1 (K), D127.1 (K), D128.1 (K), U2.5 (GRID16)
/SEG1: D1.2 (A), D9.2 (A), D17.2 (A), D25.2 (A), D33.2 (A), D41.2 (A), D49.2 (A), D57.2 (A), D65.2 (A), D73.2 (A), D81.2 (A), D89.2 (A), D97.2 (A), D105.2 (A), D113.2 (A), D121.2 (A), U2.9 (SEG1)
/SEG2: D2.2 (A), D10.2 (A), D18.2 (A), D26.2 (A), D34.2 (A), D42.2 (A), D50.2 (A), D58.2 (A), D66.2 (A), D74.2 (A), D82.2 (A), D90.2 (A), D98.2 (A), D106.2 (A), D114.2 (A), D122.2 (A), U2.10 (SEG2)
/SEG3: D3.2 (A), D11.2 (A), D19.2 (A), D27.2 (A), D35.2 (A), D43.2 (A), D51.2 (A), D59.2 (A), D67.2 (A), D75.2 (A), D83.2 (A), D91.2 (A), D99.2 (A), D107.2 (A), D115.2 (A), D123.2 (A), U2.11 (SEG3)
/SEG4: D4.2 (A), D12.2 (A), D20.2 (A), D28.2 (A), D36.2 (A), D44.2 (A), D52.2 (A), D60.2 (A), D68.2 (A), D76.2 (A), D84.2 (A), D92.2 (A), D100.2 (A), D108.2 (A), D116.2 (A), D124.2 (A), U2.12 (SEG4)
/SEG5: D5.2 (A), D13.2 (A), D21.2 (A), D29.2 (A), D37.2 (A), D45.2 (A), D53.2 (A), D61.2 (A), D69.2 (A), D77.2 (A), D85.2 (A), D93.2 (A), D101.2 (A), D109.2 (A), D117.2 (A), D125.2 (A), U2.13 (SEG5)
/SEG6: D6.2 (A), D14.2 (A), D22.2 (A), D30.2 (A), D38.2 (A), D46.2 (A), D54.2 (A), D62.2 (A), D70.2 (A), D78.2 (A), D86.2 (A), D94.2 (A), D102.2 (A), D110.2 (A), D118.2 (A), D126.2 (A), U2.14 (SEG6)
/SEG7: D7.2 (A), D15.2 (A), D23.2 (A), D31.2 (A), D39.2 (A), D47.2 (A), D55.2 (A), D63.2 (A), D71.2 (A), D79.2 (A), D87.2 (A), D95.2 (A), D103.2 (A), D111.2 (A), D119.2 (A), D127.2 (A), U2.15 (SEG7)
/SEG8: D8.2 (A), D16.2 (A), D24.2 (A), D32.2 (A), D40.2 (A), D48.2 (A), D56.2 (A), D64.2 (A), D72.2 (A), D80.2 (A), D88.2 (A), D96.2 (A), D104.2 (A), D112.2 (A), D120.2 (A), D128.2 (A), U2.16 (SEG8)
CONF-0: JP6.1 (A), U1.13 (PC3)
CONF-1: JP7.1 (A), U1.14 (PC4)
CONF-2: JP8.1 (A), U1.15 (PC5)
CONF-3: JP9.1 (A), U1.16 (PC6)
CONF-4: JP10.1 (A), U1.17 (PC7)
CONF-5: JP11.1 (A), U1.19 (PD2)
CONF-6: JP12.1 (A), U1.20 (PD3)
DATA_IN: J1.3, JP1.2 (B), JP4.1 (A), U1.3 (PD6)
DATA_OUT: J2.2, JP2.2 (B), JP3.1 (A), JP5.1 (A), U1.2 (PD5)
GND: C1.2, C2.2, C3.2, C4.2, C5.2, C6.2, C7.2, J1.1, J2.4, J3.1, J3.5, J4.1, J4.5, JP6.2 (B), JP7.2 (B), JP8.2 (B), JP9.2 (B), JP10.2 (B), JP11.2 (B), JP12.2 (B), TP4.1, U1.7 (VSS), U2.6 (VSS)
NRST: TP3.1, U1.4 (NRST)
unnamed: C5.1, U1.8 (VCAP)
unnamed: J1.2, J2.3, JP5.2 (B)
unnamed: J3.2, JP2.1 (A)
unnamed: J3.4, JP1.1 (A)
unnamed: J4.2, JP3.2 (B)
unnamed: J4.4, JP4.2 (B)
unnamed: TP5.1, U1.1 (PD4)
unnamed: TP6.1, U1.5 (PA1)
unnamed: TP7.1, U1.6 (PA2)
unnamed: TP8.1, U1.10 (PA3)
SWIM: TP2.1, U1.18 (PD1)
TM1610-CLK: R1.2, TP10.1, U1.11 (PB5), U2.8 (SCLK)
TM1610-DIN: R2.2, TP9.1, U1.12 (PB4), U2.7 (DIN)

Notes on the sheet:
3mm Push Rivet
SEG A
SEG F
SEG C
SEG T
SEG S
SEG R
SEG P
SEG N
SEG M
SEG K
SEG H
SEG G
SEG E
SEG D
SEG B
Bulk Capacitance
SWIM Programming
Tooling
Fiducial
SEG U
Data Top
Data Bottom
Config Selector
Certifications
LED Drive
Microcontroller

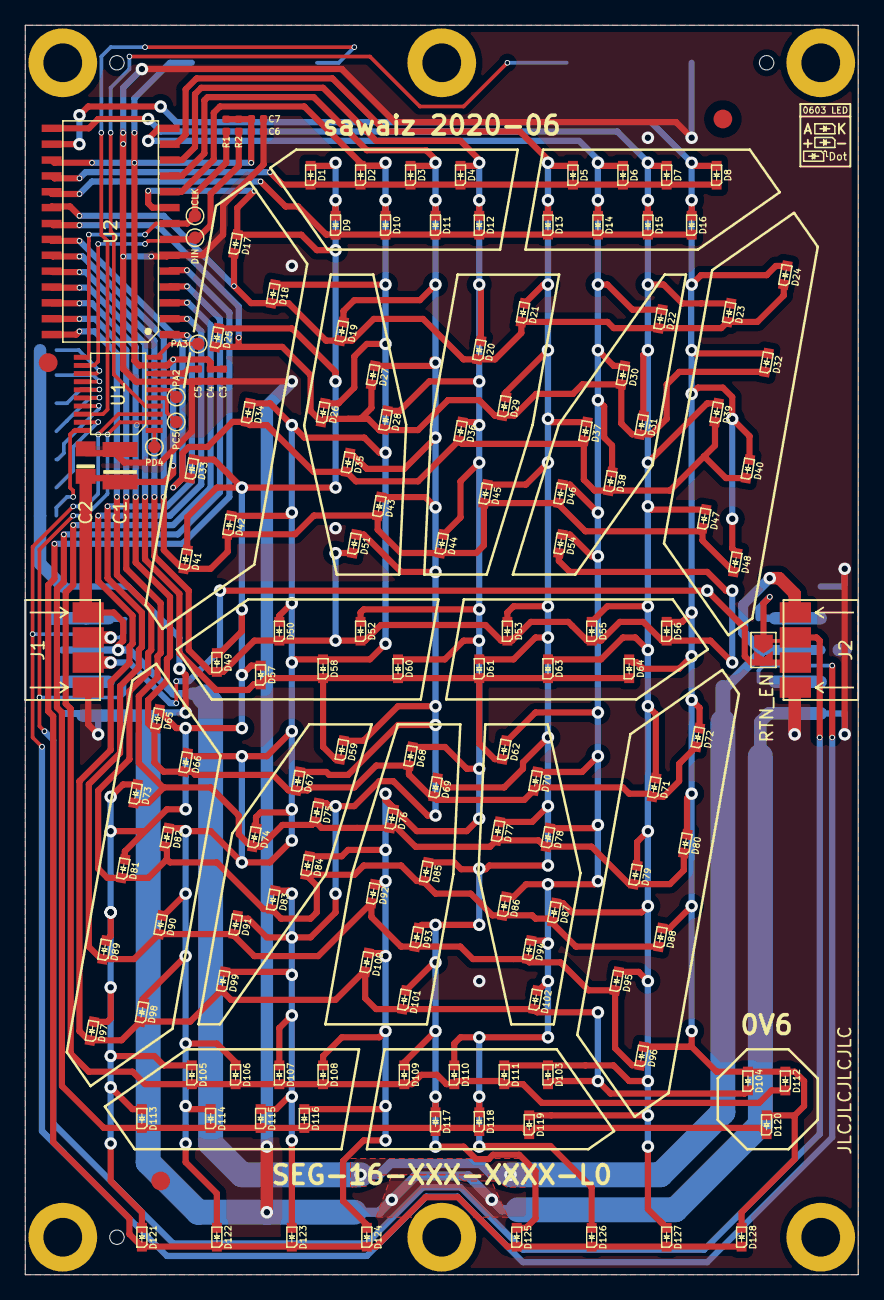
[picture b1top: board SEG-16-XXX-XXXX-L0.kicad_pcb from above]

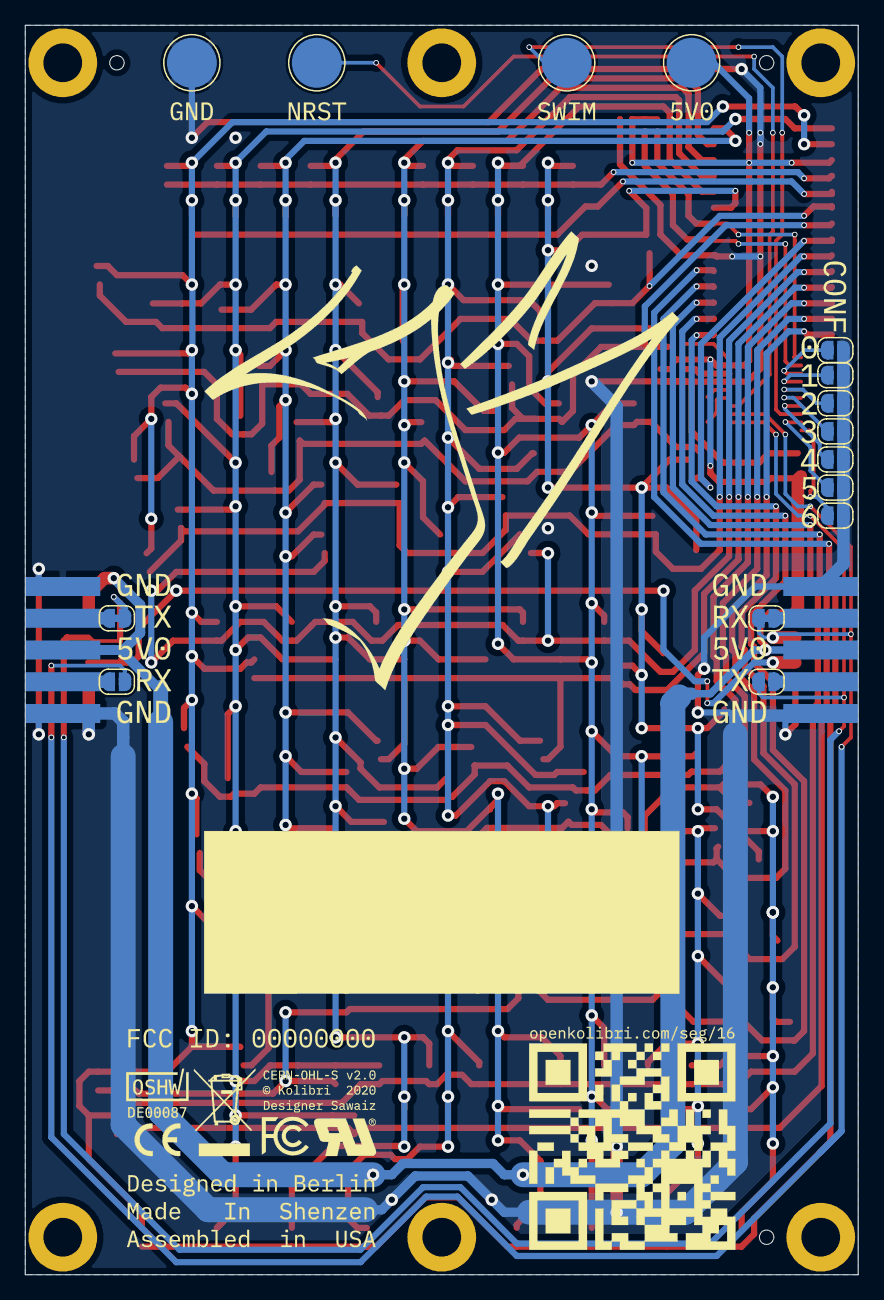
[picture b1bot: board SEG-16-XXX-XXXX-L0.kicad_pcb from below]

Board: 2 copper layers, 66.7 x 100.0 mm, 191 parts (31 on the bottom side), 49 nets.

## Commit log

2020-06-19 Updated to 0V6 changed images
2020-06-20 Changed TM1640 picture, updated minimal programer image
2020-06-23 Added sections
2020-06-24 Added alt text, finialized technical manual
2020-06-24 Fixed frimware paths in doc
2020-06-24 TOC links with mispellings fixed
2020-06-24 Remove duplicate readme
2020-06-24 Correct voltage spelling
2020-06-24 Correct 'programmer'/'programming' spelling
2020-06-24 Arbitrary additional spacing removal that my editor does
2020-06-24 More spelling fixes
2020-06-24 Fix userGuide reference
2020-06-25 Added current profiles for B14-B4
2020-06-26 Imporved images
2020-06-26 Removed extra gif, fixed linking of main gif
2020-06-26 A few stragglers
2020-06-26 Fixed user guide link, moved into docs subfolder
2020-06-26 Fix certification spelling
2020-06-27 units and numbers are now (hopefully all of them) consistently in monospace for emphisis
2020-06-27 Added buadrate selection suppourtin firmware and docs
2020-06-27 User guide progress
2020-06-28 Update readme.md
    Spelling and grammar changes in Configuration section
2020-06-28 Update userGuide.md
    Spelling and grammatical corrections
2020-06-28 Added gifs to userGuide
2020-06-28 Fixed links and document flow
2020-06-28 Replace renders with pictures
2020-06-28 Current test stand info added
2020-06-28 Cropped advanced programer image correctly
2020-06-28 Updated label image
2020-06-28 Updated mini current table
2020-06-29 Removed extra buffer
2020-06-30 Update readme.md
    Spelling fixes in Configuration section
2020-10-05 Update userGuide.md
    Verified cmd/bat file commands.
2020-10-16 Added WDT to display code
2021-01-20 Fix status of the pad #4 in the documentation
2021-01-25 Change ""nM" to "nm" in BOM
2021-01-28 Reverted version to kicad 5.x, fixed OSHW Marking, added better led markings and legend
2021-02-20 Fixed serial spelling

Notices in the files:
readme.md:
Licence:
The product was designed by Sawaiz Syed for Kolibri who owns the copyright. Everything is released under permissive copyleft licenses, and copies of all licenses are included.
Sector | License | Verison
Hardware | [CERN-OHL-S] | 2.0
Firmware | [GNU GPL] | 3.0
Documentation | [CC BY-SA] | 4.0
Copies of all licenses are required with the distribution of files. All files are available in easy-to-modify types for remixing. Please purchase original products from Kolibri to support further products,
[CERN-OHL-S]: ./pcb/LICENSE
[GNU GPL]: ./firmware/LICENSE
